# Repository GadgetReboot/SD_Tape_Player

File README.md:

# SD_Tape_Player
Play computer cassette data audio files from a micro SD card with Arduino Nano<BR><BR>
<br><br>
This pcb was tested with the Arduino sketch for CASDuino 1.24 obtained here http://arduitape.blogspot.com/2020/08/new-castzxduino-firmware.html

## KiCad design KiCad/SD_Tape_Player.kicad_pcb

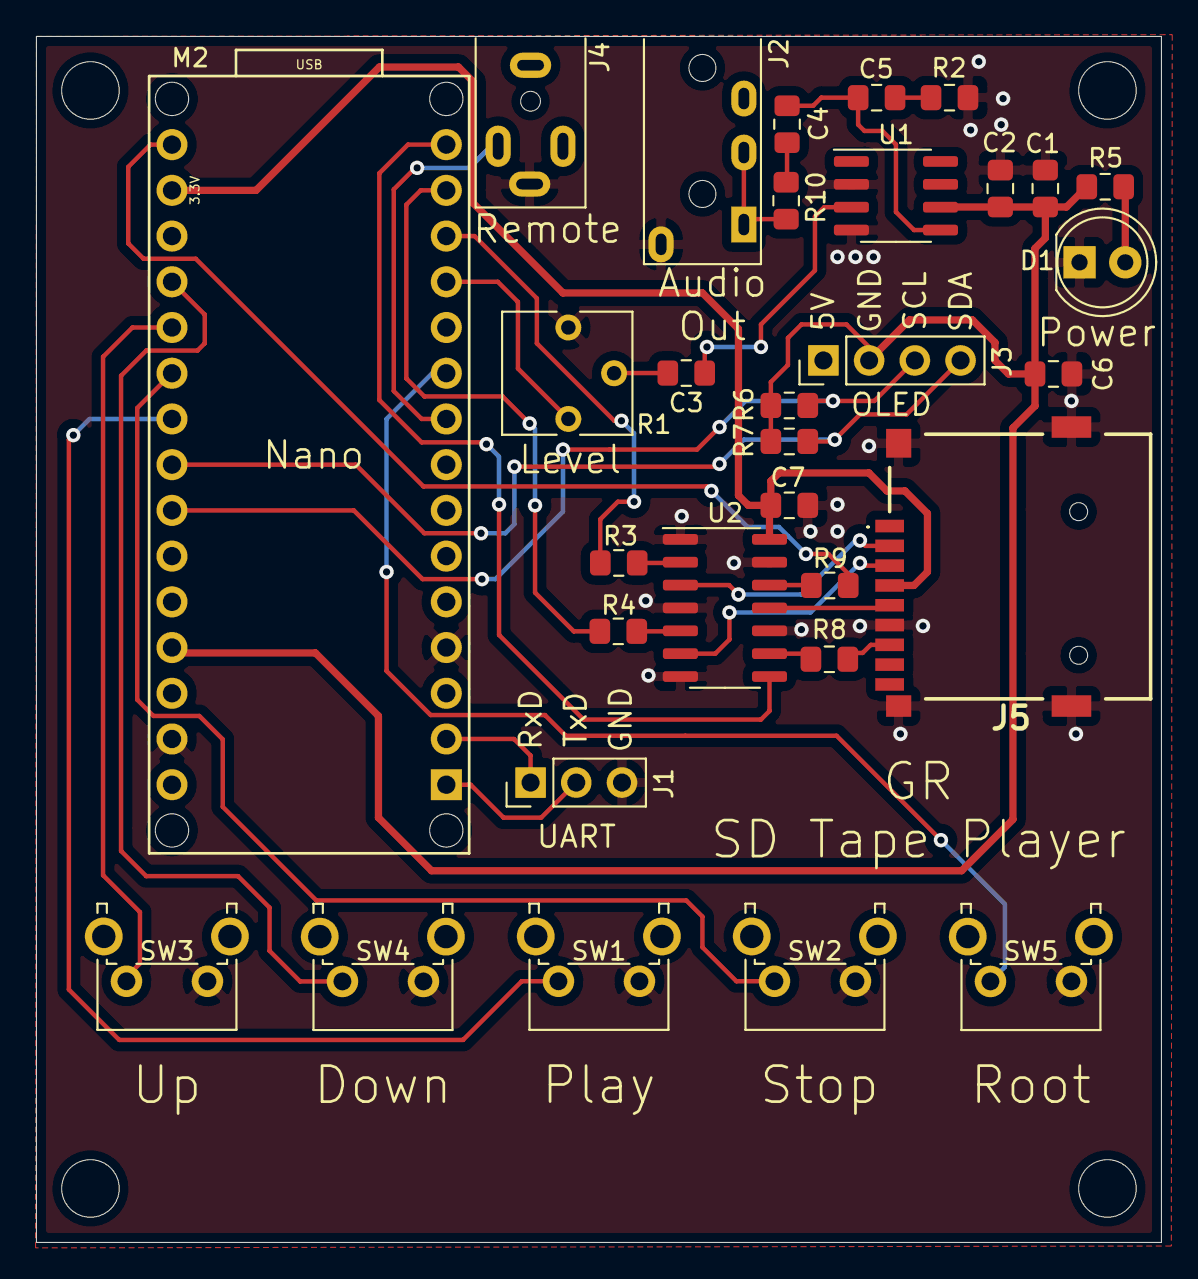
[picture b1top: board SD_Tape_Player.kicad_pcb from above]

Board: 2 copper layers, 62.5 x 67.0 mm, 35 parts (0 on the bottom side), 33 nets.

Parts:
C1, C4: 10uF; C_0805_2012Metric_Pad1.15x1.40mm_HandSolder
C2, C7: 100nF; C_0805_2012Metric_Pad1.15x1.40mm_HandSolder
C3, C6: 1uF; C_0805_2012Metric_Pad1.15x1.40mm_HandSolder
C5: 47nF; C_0805_2012Metric_Pad1.15x1.40mm_HandSolder
D1: LED_Small_ALT; LED_D5.0mm
J1: UART; PinHeader_1x03_P2.54mm_Vertical
J2: AudioJack; Jack_3.5mm_PJ320A_Horizontal
J3: Conn_01x04; PinHeader_1x04_P2.54mm_Vertical
J4: 2.5mm Jack; Jack_2.5mm_PJ210B
J5: Micro_SD TFP09-2-12B; TFP09212B
M2: Arduino_Nano_Socket
MH1, MH2, MH3, MH4: MountingHole; MountingHole_3.2mm_M3
R1: 10K; Potentiometer_Vishay_T73YP_Vertical
R2: 10r; R_0805_2012Metric_Pad1.15x1.40mm_HandSolder
R3, R4, R5, R8, R9: 3.3K; R_0805_2012Metric_Pad1.15x1.40mm_HandSolder
R6, R7: 10K; R_0805_2012Metric_Pad1.15x1.40mm_HandSolder
R10: 100r; R_0805_2012Metric_Pad1.15x1.40mm_HandSolder
SW1, SW2, SW3, SW4, SW5: B3F-3100; SW_Tactile_SPST_Angled_PTS645Vx31-2LFS
U1: LM386; SOIC-8_3.9x4.9mm_P1.27mm
U2: 74LVC125; SOIC-14_3.9x8.7mm_P1.27mm

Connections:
+3V3: C7.1, J5.4, M2.3V3, U2.14
+5V: C1.2, C2.1, C6.1, J3.2, M2.5V, R5.2, R6.1, R7.1, U1.6
/Audio_Out: M2.D9, R1.1
/Down: M2.A0, SW4.2
/MISO: M2.D12, U2.8
/MOSI: M2.D11, R4.2
/Play: M2.A3, SW1.2
/Remote_Start: J4.T, M2.D6
/Root: M2.D7, SW5.2
/RxD: J1.1, M2.D0
/SCK: M2.D13, R9.2
/SCL: J3.3, M2.A5, R6.2
/SDA: J3.4, M2.A4, R7.2
/Stop: M2.A2, SW2.2
/TxD: J1.2, M2.D1
/Up: M2.A1, SW3.2
/~CS: M2.D10, R3.2
GNDREF: C1.1, C2.2, C6.2, C7.2, D1.1, J1.3, J2.S, J3.1, J4.S, J5.6, J5.11, M2.GND1, M2.GND2, R1.3, R2.2, SW1.1, SW2.1, SW3.1, SW4.1, SW5.1, U1.2, U1.4, U2.1, U2.4, U2.7, U2.10, U2.13
unnamed: C3.1, U1.3
unnamed: C3.2, R1.2
unnamed: C4.1, C5.1, U1.5
unnamed: C4.2, R10.2
unnamed: C5.2, R2.1
unnamed: D1.2, R5.1
unnamed: J2.R1, J2.T, R10.1
unnamed: J5.2, U2.3
unnamed: J5.3, U2.6
unnamed: J5.5, U2.11
unnamed: J5.7, R8.2
unnamed: R3.1, U2.2
unnamed: R4.1, U2.5
unnamed: R8.1, U2.9
unnamed: R9.1, U2.12
